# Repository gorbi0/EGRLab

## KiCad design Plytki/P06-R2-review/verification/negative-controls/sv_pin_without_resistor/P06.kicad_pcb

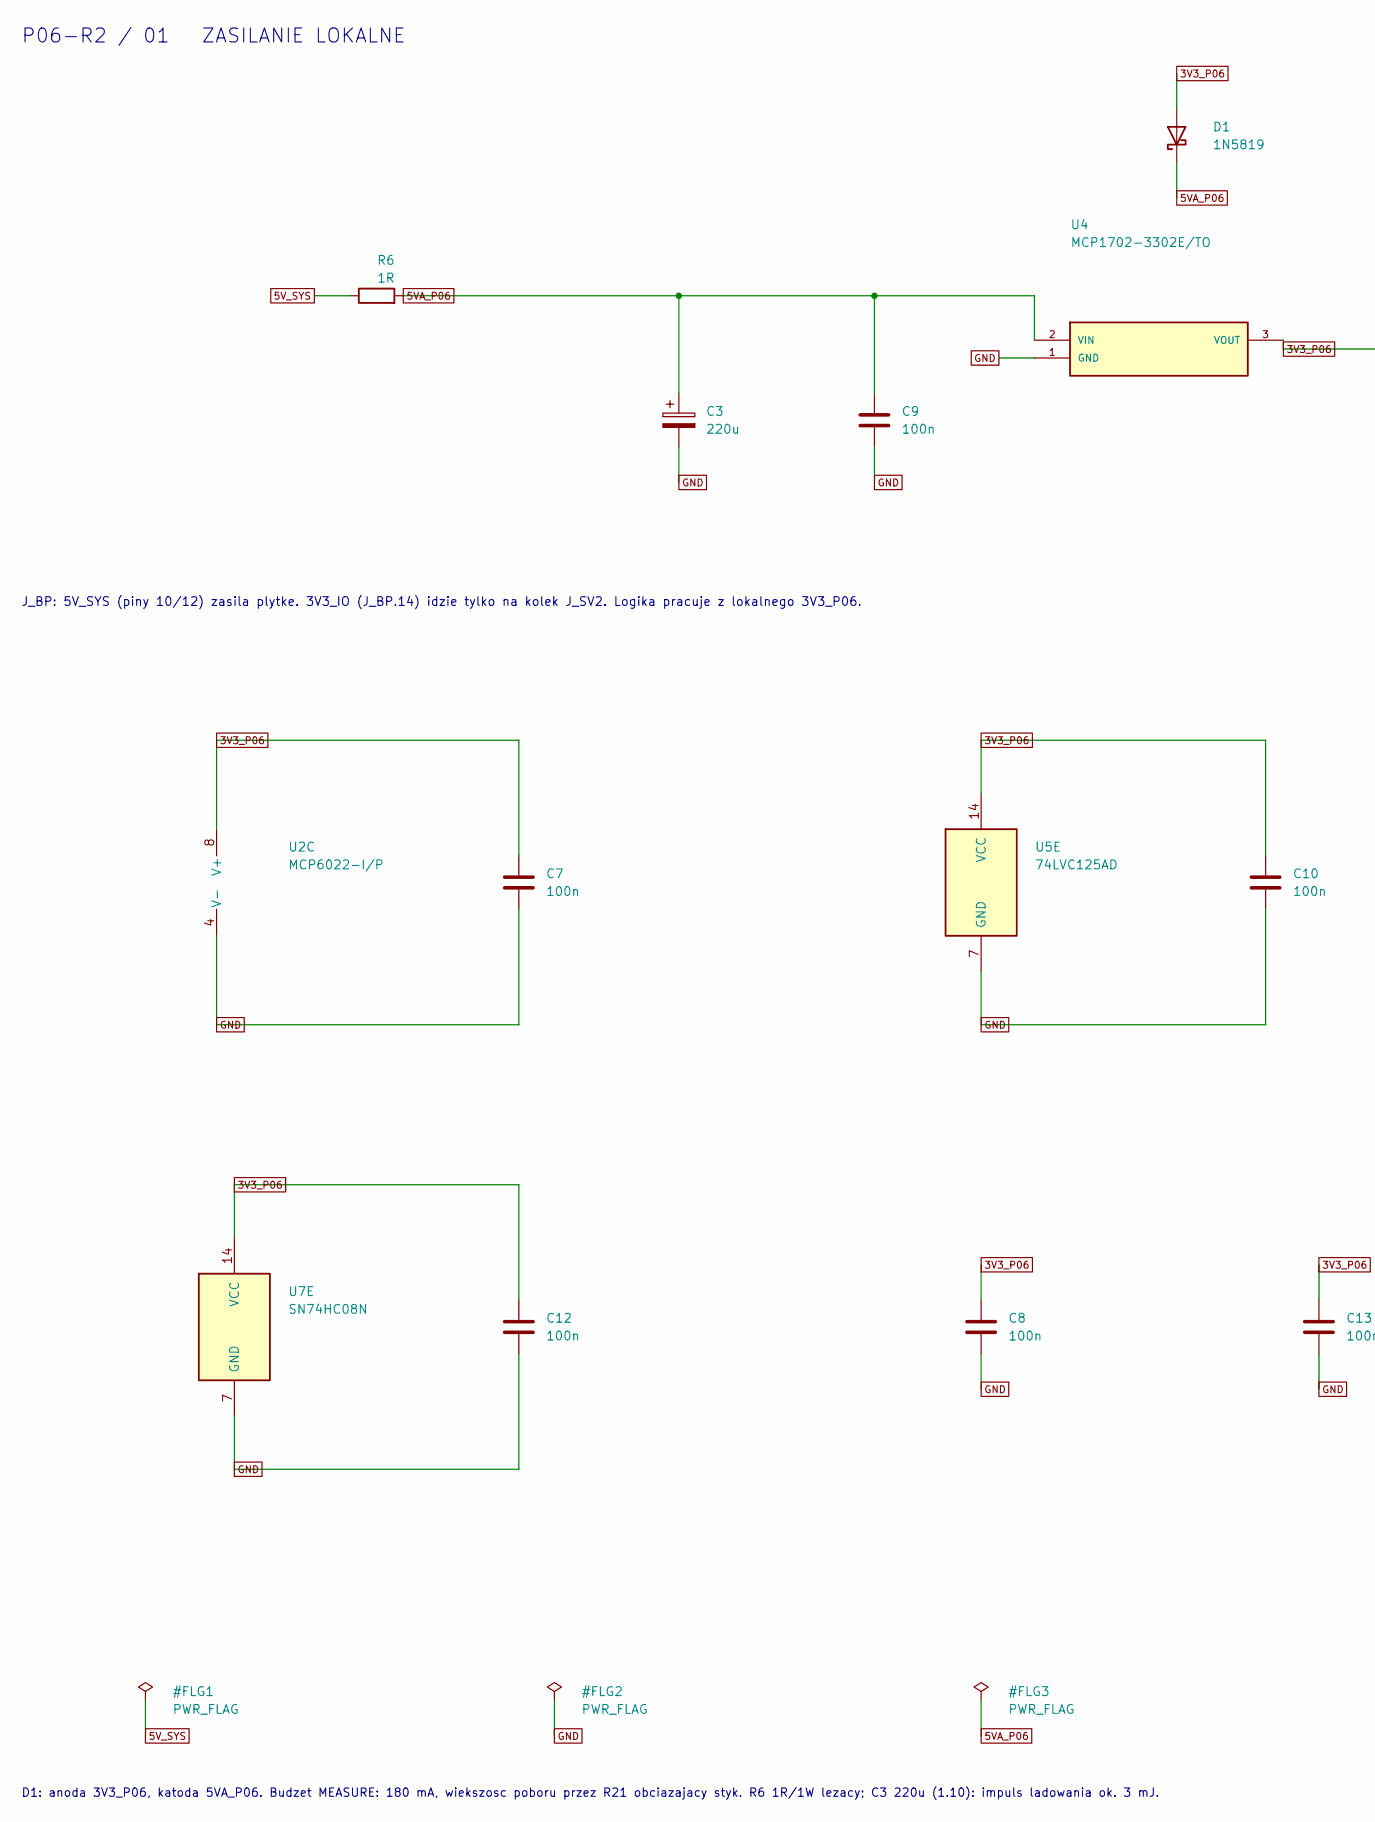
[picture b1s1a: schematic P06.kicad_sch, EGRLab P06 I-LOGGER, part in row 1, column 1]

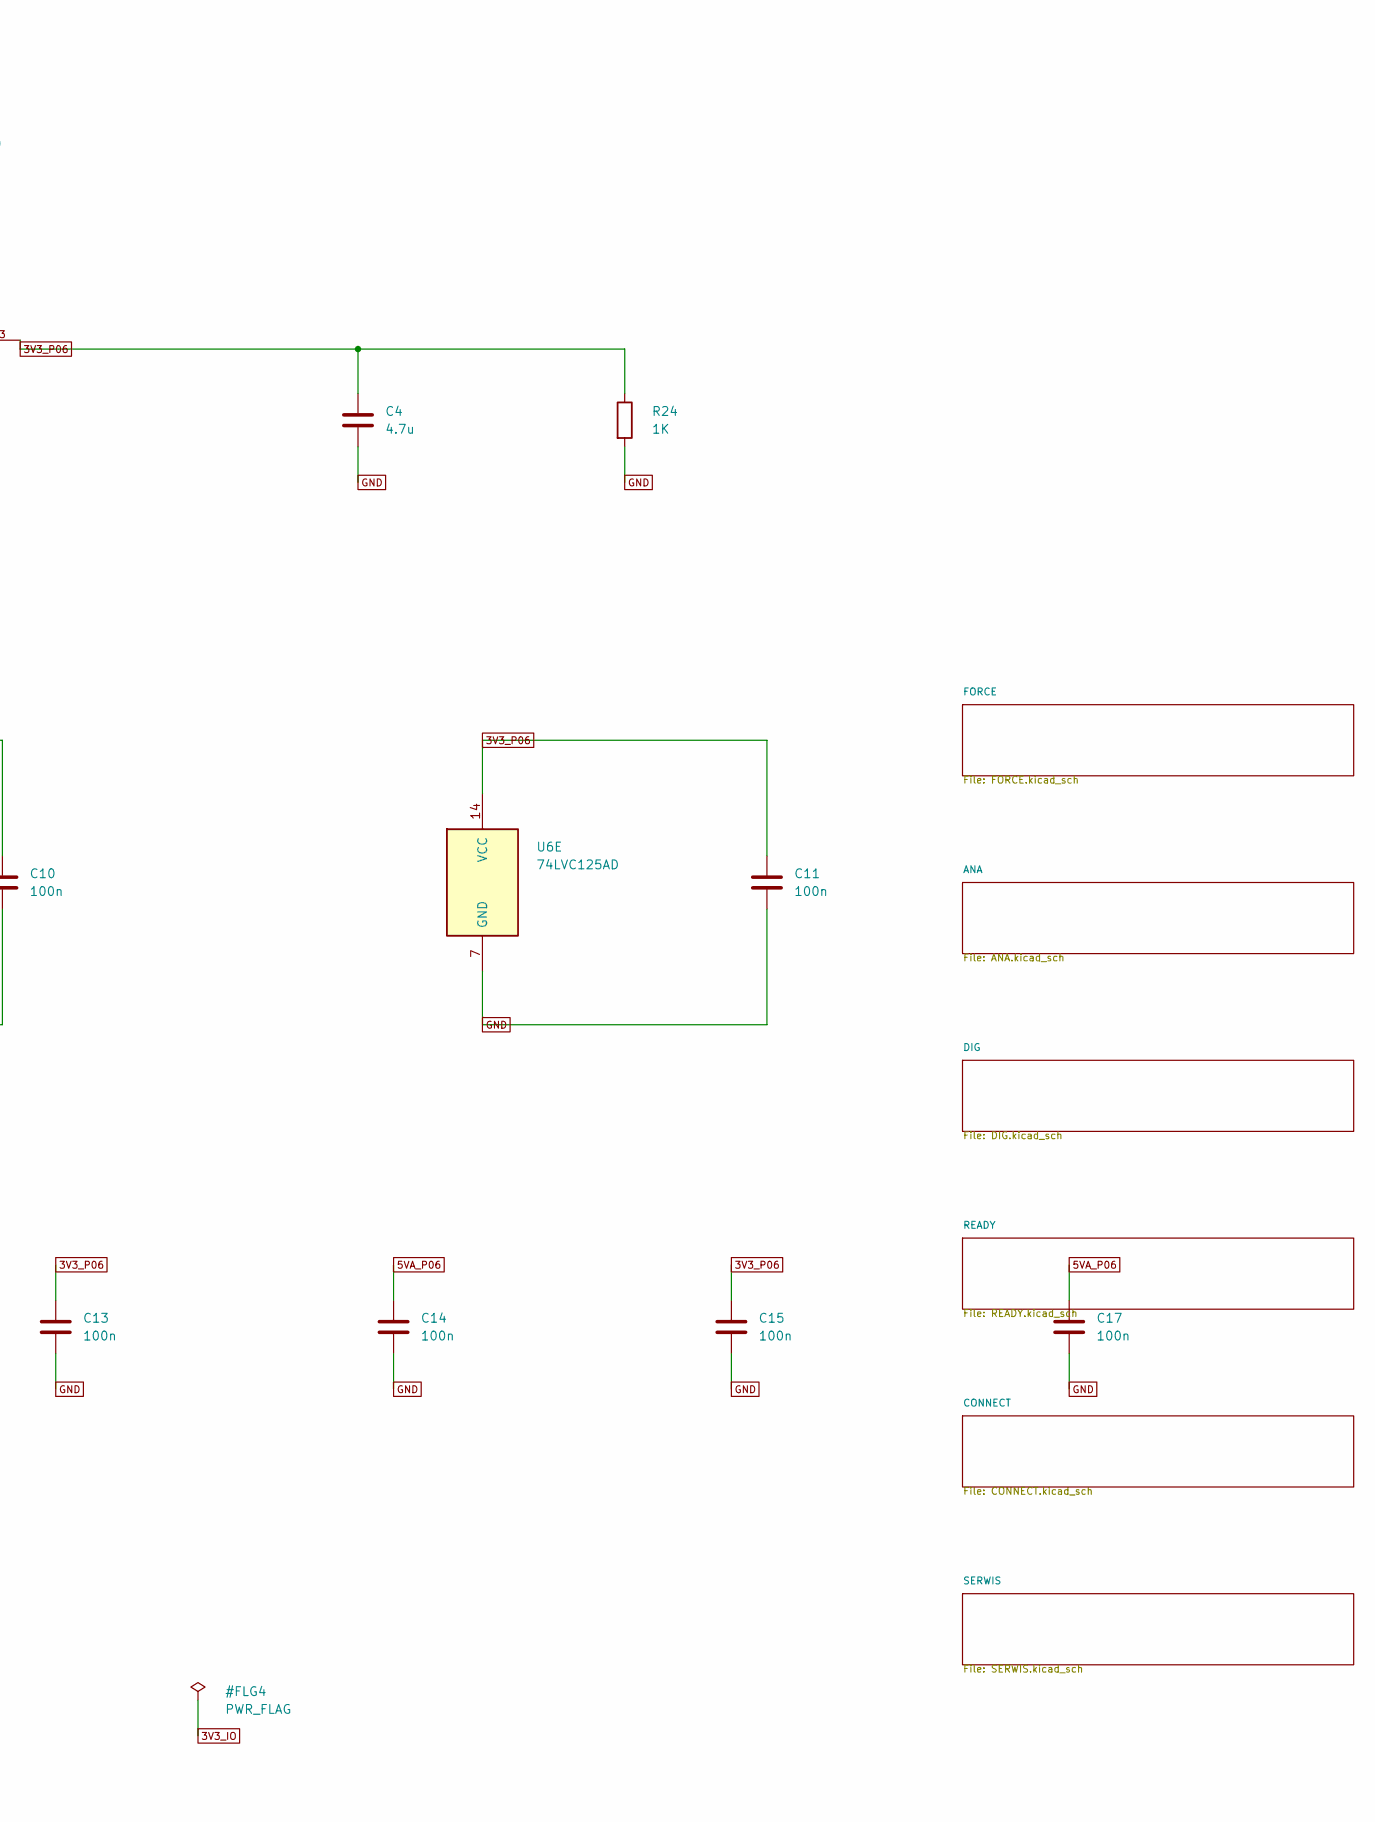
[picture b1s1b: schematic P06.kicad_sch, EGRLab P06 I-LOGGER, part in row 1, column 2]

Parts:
C3: 220u; CP_Radial_D6.3mm_P2.50mm; MPN EEUFR1C221
C4: 4.7u; C_1206_3216Metric_Pad1.33x1.80mm_HandSolder; MPN SMD 1206 X7R 25V 10% 4.7u
C7, C8, C9, C10, C11, C12, C13, C14, C15, C17: 100n; C_1206_3216Metric_Pad1.33x1.80mm_HandSolder; MPN SMD 1206 X7R 50V 10% 100n
D1: 1N5819; D_DO-41_SOD81_P10.16mm_Horizontal; MPN 1N5819
R6: 1R; R_Axial_DIN0411_L9.9mm_D3.6mm_P15.24mm_Horizontal; MPN KNP01U-1R (1R 1W wirewound, body 3x9mm)
R24: 1K; R_1206_3216Metric_Pad1.30x1.75mm_HandSolder; MPN RC1206FR-071KL
U2: MCP6022-I/P; DIP-8_W7.62mm; MPN MCP6022-I/P
U4: MCP1702-3302E/TO; TO-92_Inline_Wide; MPN MCP1702-3302E/TO
U5, U6: 74LVC125AD; SOIC-14_3.9x8.7mm_P1.27mm; MPN 74LVC125AD,118 (Nexperia)
U7: SN74HC08N; DIP-14_W7.62mm; MPN SN74HC08N

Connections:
3V3_P06: C4.1, C7.1, C8.1, C10.1, C11.1, C12.1, C13.1, C15.1, D1.2 (A), R24.1, U2.8 (V+), U4.3 (VOUT), U5.14 (VCC), U6.14 (VCC), U7.14 (VCC); also elsewhere on the board
5VA_P06: C3.1, C9.1, C14.1, C17.1, D1.1 (K), R6.2, U4.2 (VIN); also elsewhere on the board
/ANA/I_DIV: U2.3 (+); also elsewhere on the board
ADC_BUF: U2.1, U2.2 (-); also elsewhere on the board
GND: C3.2, C4.2, C7.2, C8.2, C9.2, C10.2, C11.2, C12.2, C13.2, C14.2, C15.2, C17.2, R24.2, U2.4 (V-), U4.1 (GND), U5.7 (GND), U6.7 (GND), U7.7 (GND); also elsewhere on the board
REF25: U2.5 (+); also elsewhere on the board
REF_BUF: U2.6 (-), U2.7; also elsewhere on the board

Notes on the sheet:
J_BP: 5V_SYS (piny 10/12) zasila plytke. 3V3_IO (J_BP.14) idzie tylko na kolek J_SV2. Logika pracuje z lokalnego 3V3_P06.
D1: anoda 3V3_P06, katoda 5VA_P06. Budzet MEASURE: 180 mA, wiekszosc poboru przez R21 obciazajacy styk. R6 1R/1W lezacy; C3 220u (1.10): impuls ladowania ok. 3 mJ.
P06-R2 / 01 ZASILANIE LOKALNE

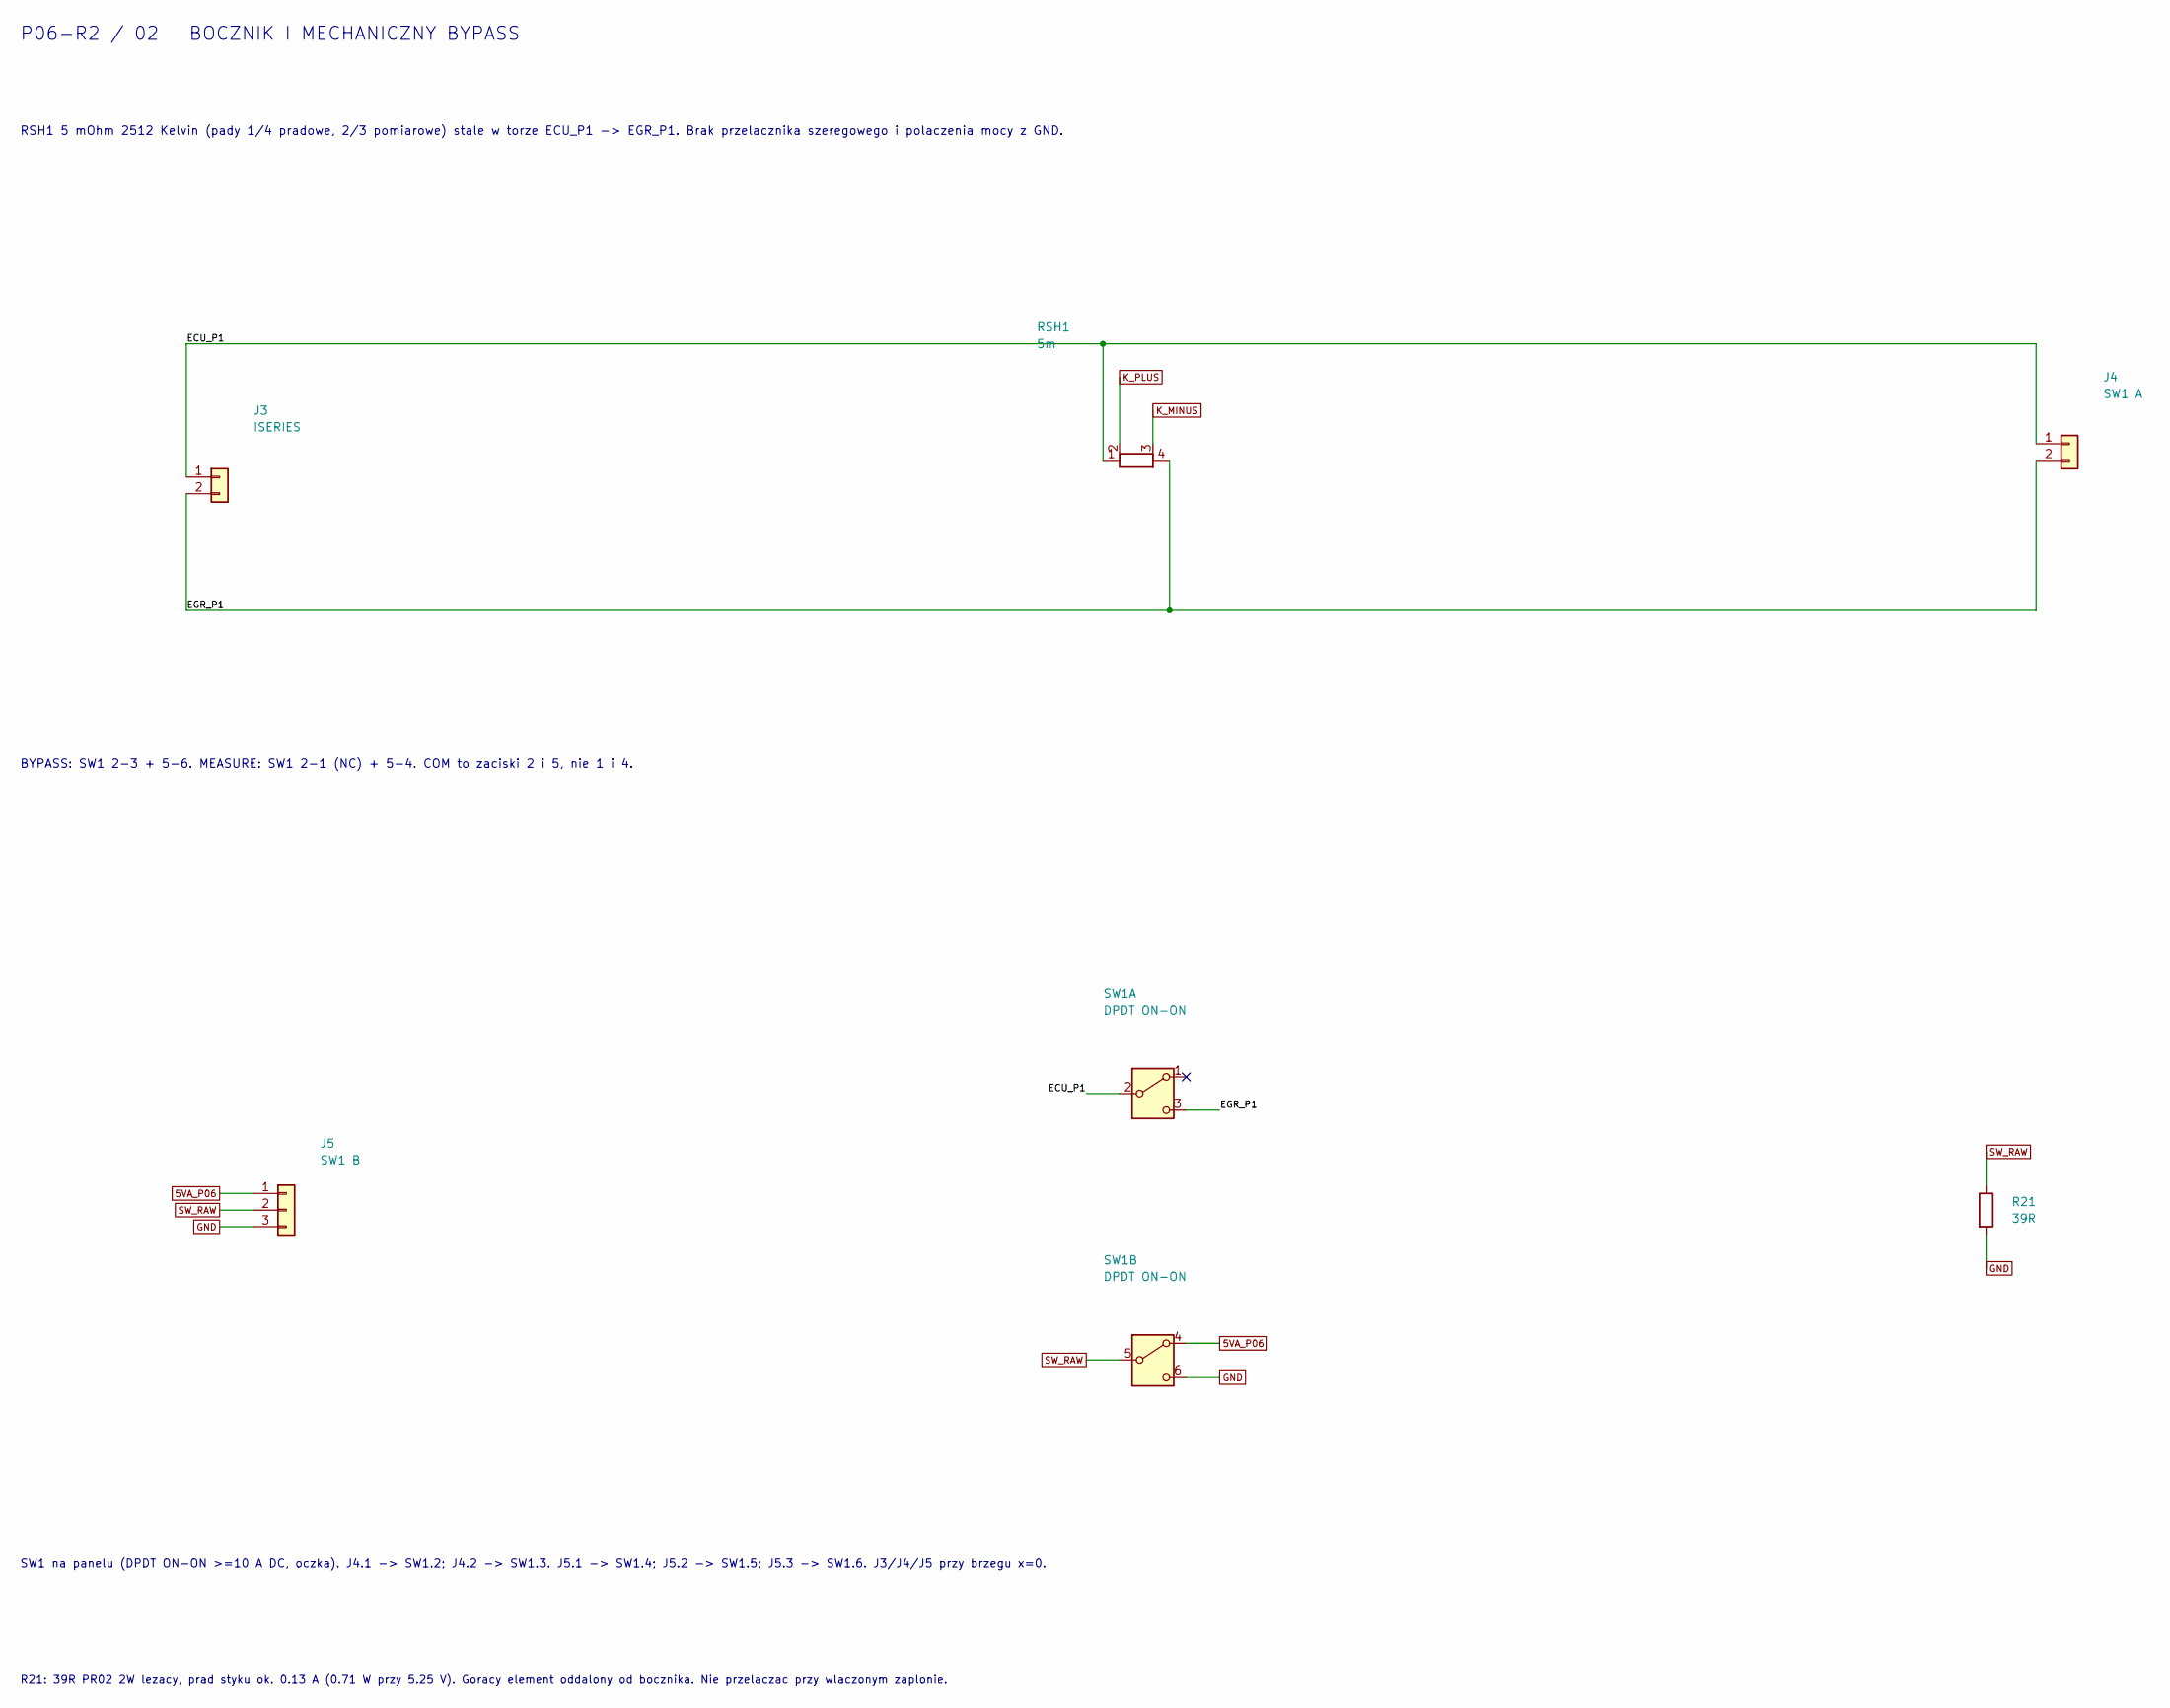
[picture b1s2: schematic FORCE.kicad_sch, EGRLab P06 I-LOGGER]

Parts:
J3: ISERIES; PTH_ISERIES; MPN Soldered harness
J4: SW1 A; PTH_BYPASS; MPN Soldered harness
J5: SW1 B; PTH_SWSTATUS; MPN Soldered harness
R21: 39R; R_PR02_P17.78; MPN PR02000203909JA100 (Vishay PR02 39R 5% 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
RSH1: 5m; R_Shunt_Vishay_WSK2512_T1.19mm_SenseE1.70; MPN WSK25125L000FEA (Vishay WSK2512, 5 mOhm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
SW1: DPDT ON-ON; OFFBOARD; MPN DPDT ON-ON panel toggle >=10A 12-30VDC,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

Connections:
5VA_P06: J5.1, SW1.4 (A); also elsewhere on the board
/FORCE/ECU_P1: J3.1, J4.1, RSH1.1, SW1.2 (B)
/FORCE/EGR_P1: J3.2, J4.2, RSH1.4, SW1.3 (C)
GND: J5.3, R21.2, SW1.6 (C); also elsewhere on the board
K_MINUS: RSH1.3; also elsewhere on the board
K_PLUS: RSH1.2; also elsewhere on the board
SW_RAW: J5.2, R21.1, SW1.5 (B); also elsewhere on the board

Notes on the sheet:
RSH1 5 mOhm 2512 Kelvin (pady 1/4 pradowe, 2/3 pomiarowe) stale w torze ECU_P1 -> EGR_P1. Brak przelacznika szeregowego i polaczenia mocy z GND.
BYPASS: SW1 2-3 + 5-6. MEASURE: SW1 2-1 (NC) + 5-4. COM to zaciski 2 i 5, nie 1 i 4.
SW1 na panelu (DPDT ON-ON >=10 A DC, oczka). J4.1 -> SW1.2; J4.2 -> SW1.3. J5.1 -> SW1.4; J5.2 -> SW1.5; J5.3 -> SW1.6. J3/J4/J5 przy brzegu x=0.
R21: 39R PR02 2W lezacy, prad styku ok. 0.13 A (0.71 W przy 5.25 V). Goracy element oddalony od bocznika. Nie przelaczac przy wlaczonym zaplonie.
P06-R2 / 02 BOCZNIK I MECHANICZNY BYPASS

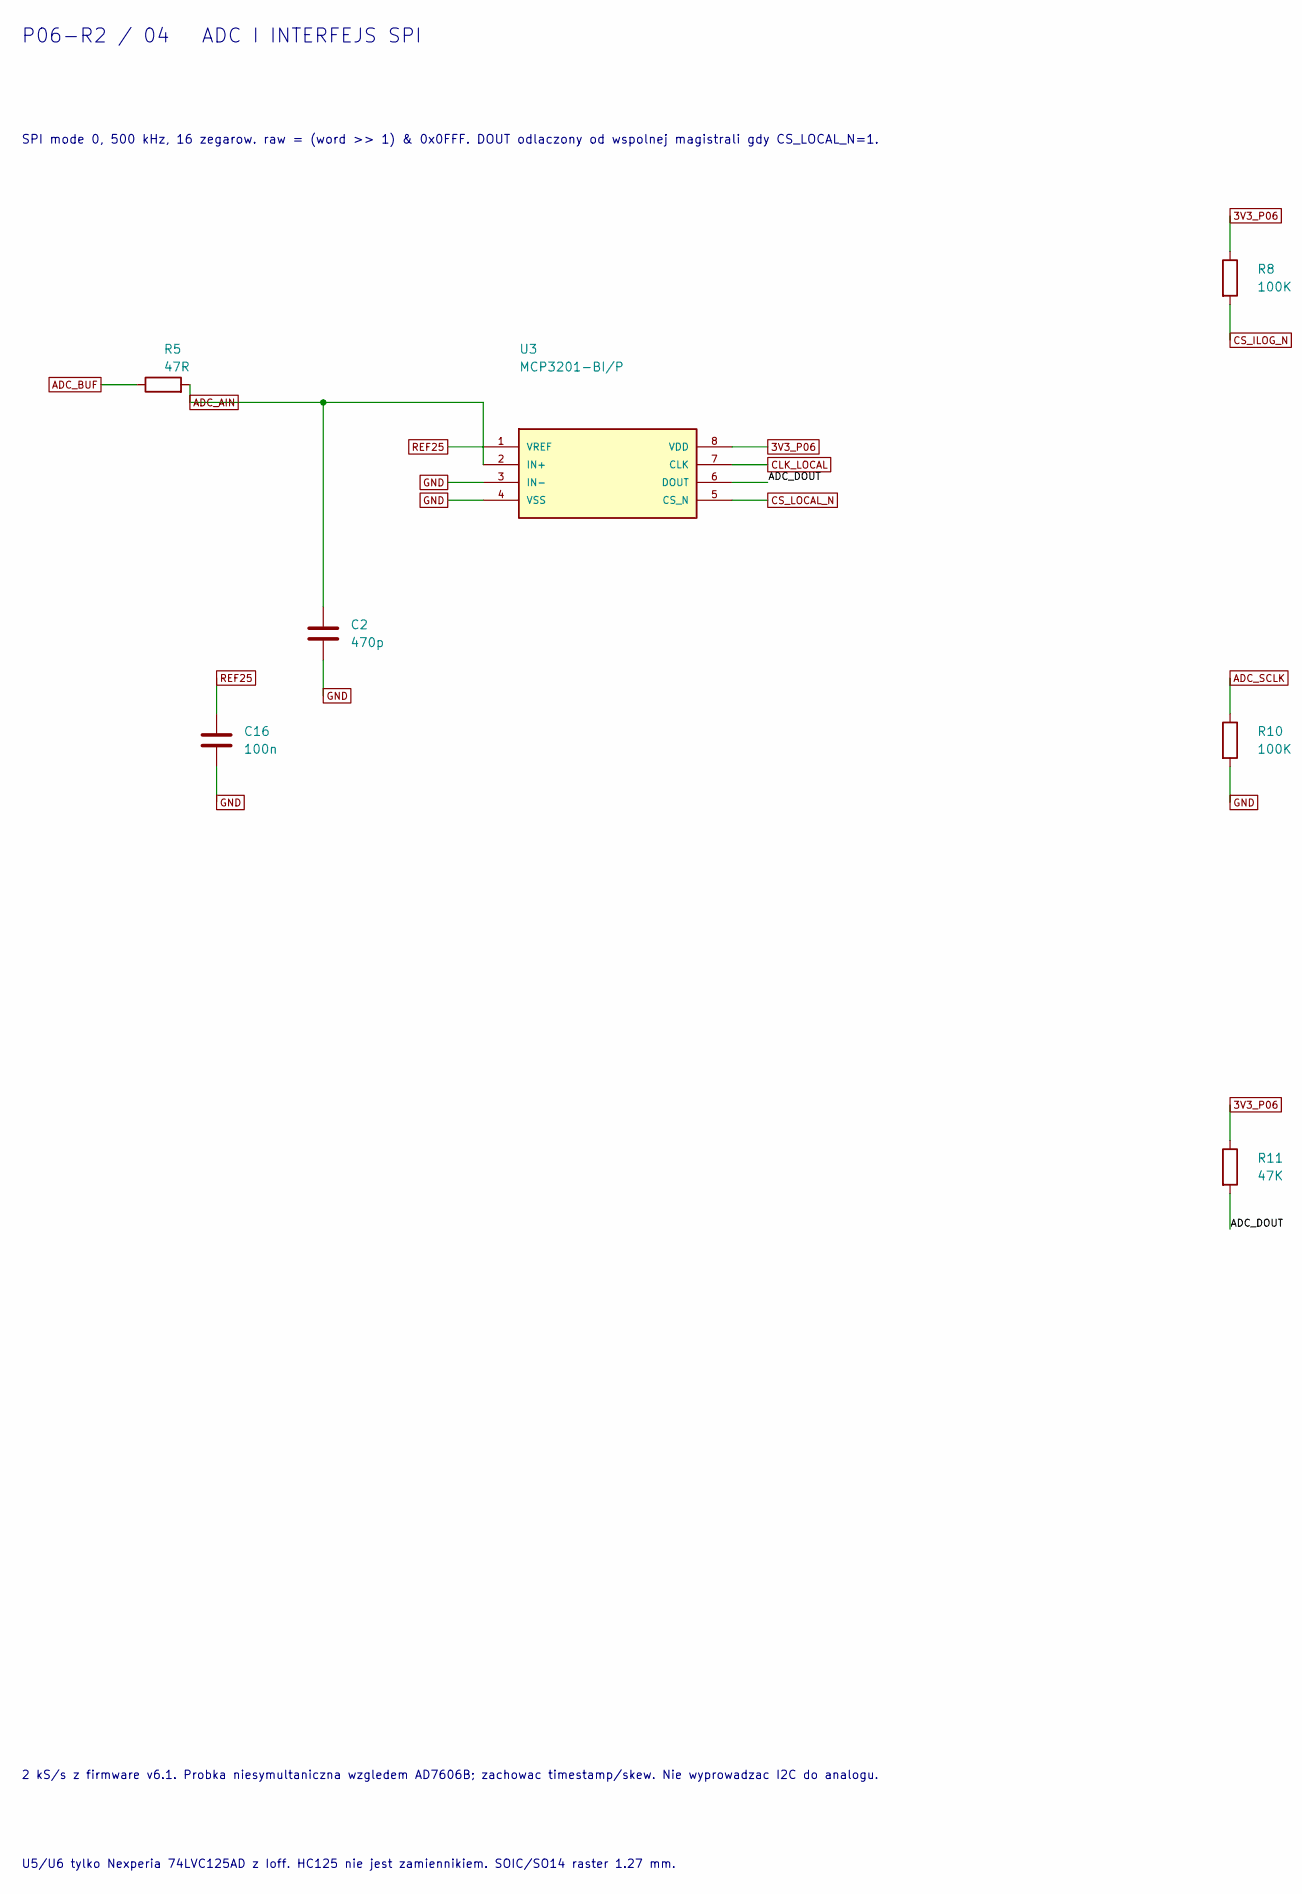
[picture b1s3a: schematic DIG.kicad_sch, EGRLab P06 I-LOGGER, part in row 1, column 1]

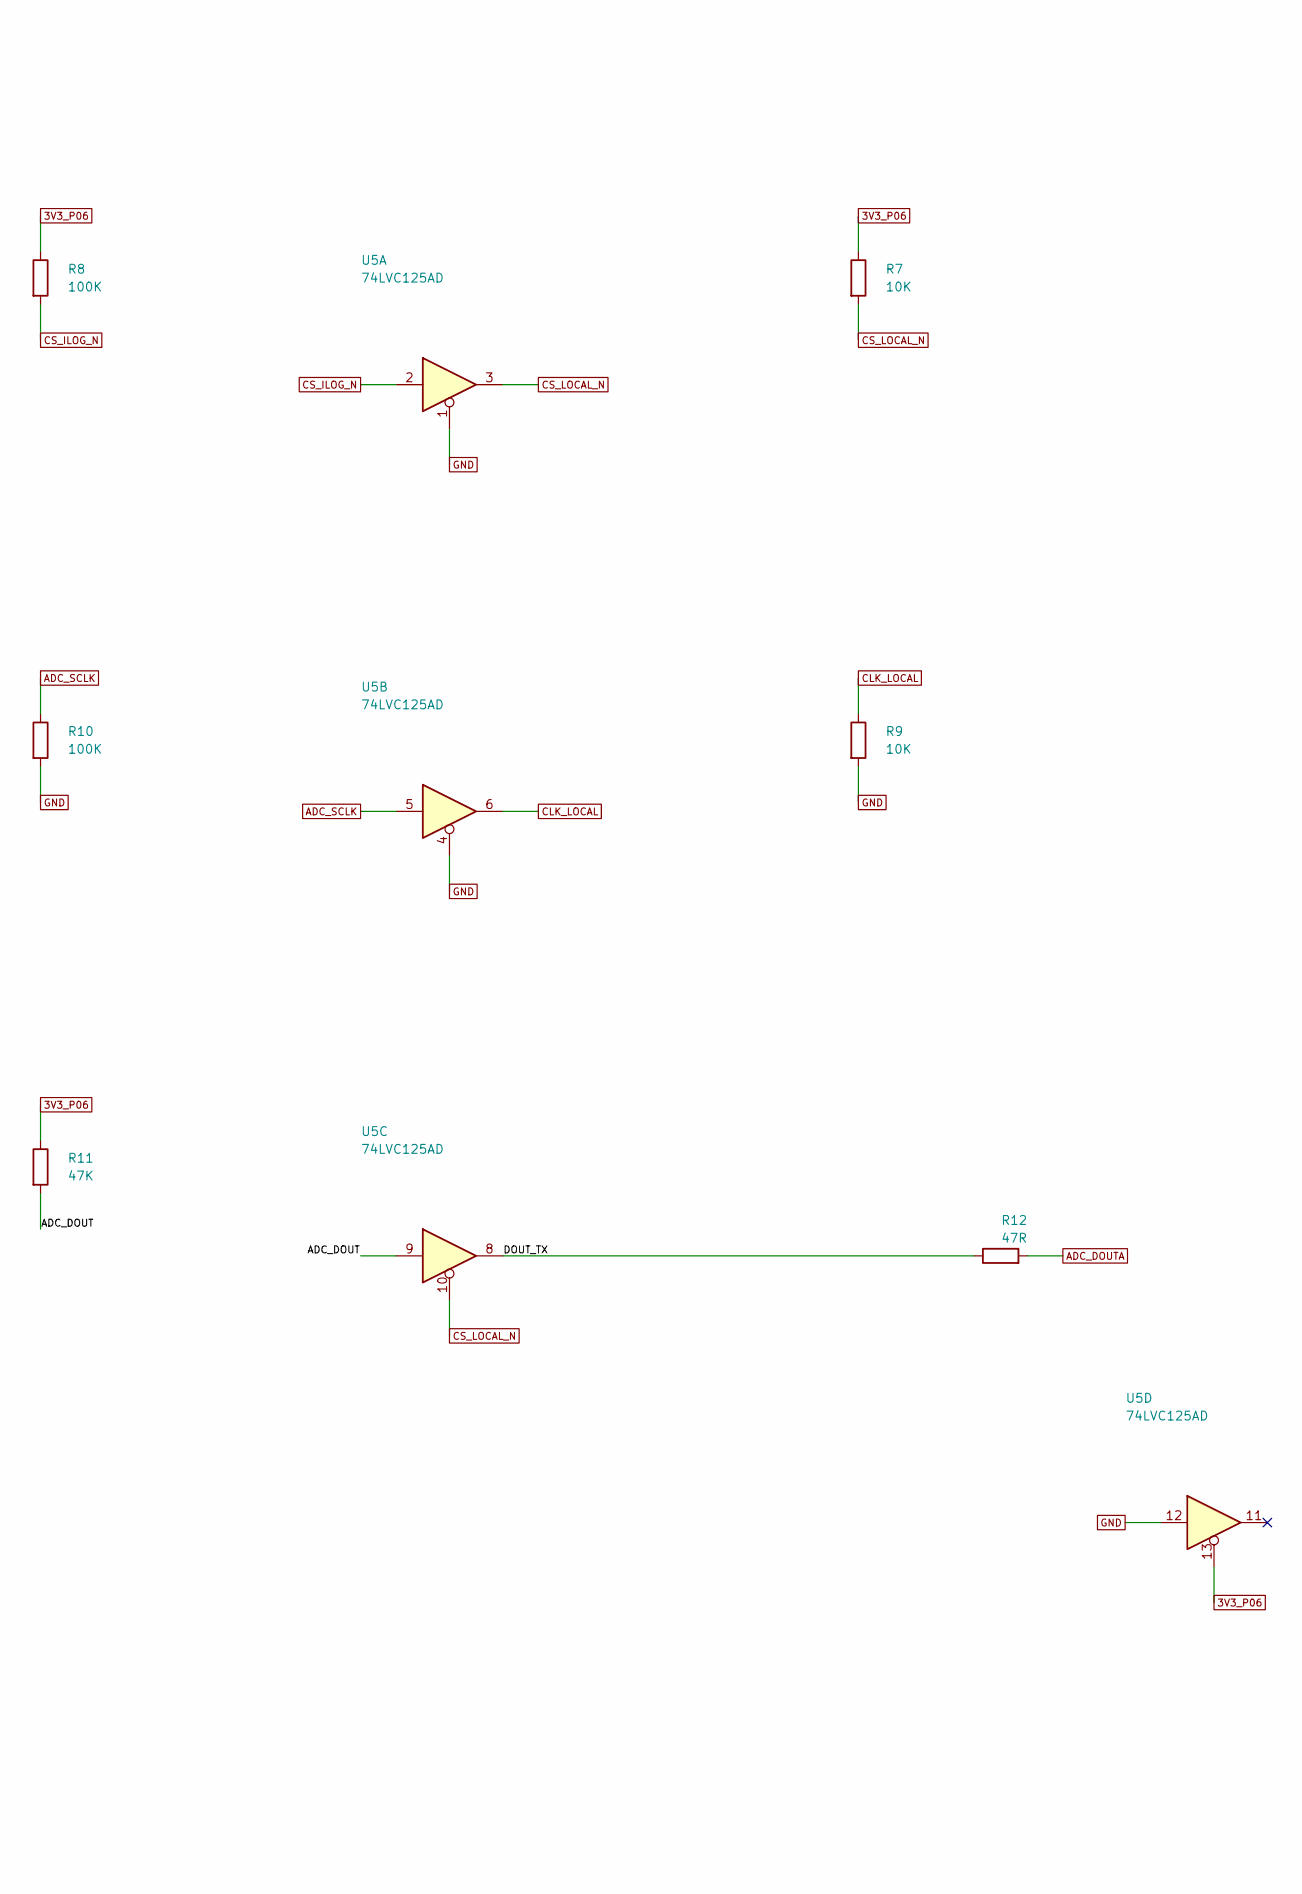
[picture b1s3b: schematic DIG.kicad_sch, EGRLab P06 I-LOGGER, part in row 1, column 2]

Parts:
C2: 470p; C_1206_3216Metric_Pad1.33x1.80mm_HandSolder; MPN SMD 1206 C0G 50V 5% 470p
C16: 100n; C_1206_3216Metric_Pad1.33x1.80mm_HandSolder; MPN SMD 1206 X7R 50V 10% 100n
R5, R12: 47R; R_1206_3216Metric_Pad1.30x1.75mm_HandSolder; MPN RC1206FR-0747RL
R7, R9: 10K; R_1206_3216Metric_Pad1.30x1.75mm_HandSolder; MPN RC1206FR-0710KL
R8, R10: 100K; R_1206_3216Metric_Pad1.30x1.75mm_HandSolder; MPN RC1206FR-07100KL
R11: 47K; R_Axial_DIN0207_L6.3mm_D2.5mm_P5.08mm_Vertical; MPN MF0207FTE-47K (Yageo MF0207 1% 0.6W, ow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
U3: MCP3201-BI/P; DIP-8_W7.62mm; MPN MCP3201-BI/P
U5: 74LVC125AD; SOIC-14_3.9x8.7mm_P1.27mm; MPN 74LVC125AD,118 (Nexperia)

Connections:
3V3_P06: R7.1, R8.1, R11.1, U3.8 (VDD), U5.13; also elsewhere on the board
/DIG/ADC_DOUT: R11.2, U3.6 (DOUT), U5.9
/DIG/DOUT_TX: R12.1, U5.8
ADC_AIN: C2.1, R5.2, U3.2 (IN+); also elsewhere on the board
ADC_BUF: R5.1; also elsewhere on the board
ADC_DOUTA: R12.2; also elsewhere on the board
ADC_SCLK: R10.1, U5.5; also elsewhere on the board
CLK_LOCAL: R9.1, U3.7 (CLK), U5.6; also elsewhere on the board
CS_ILOG_N: R8.2, U5.2; also elsewhere on the board
CS_LOCAL_N: R7.2, U3.5 (CS_N), U5.3, U5.10; also elsewhere on the board
GND: C2.2, C16.2, R9.2, R10.2, U3.3 (IN-), U3.4 (VSS), U5.1, U5.4, U5.12; also elsewhere on the board
REF25: C16.1, U3.1 (VREF); also elsewhere on the board

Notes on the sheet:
SPI mode 0, 500 kHz, 16 zegarow. raw = (word >> 1) & 0x0FFF. DOUT odlaczony od wspolnej magistrali gdy CS_LOCAL_N=1.
2 kS/s z firmware v6.1. Probka niesymultaniczna wzgledem AD7606B; zachowac timestamp/skew. Nie wyprowadzac I2C do analogu.
U5/U6 tylko Nexperia 74LVC125AD z Ioff. HC125 nie jest zamiennikiem. SOIC/SO14 raster 1.27 mm.
P06-R2 / 04 ADC I INTERFEJS SPI

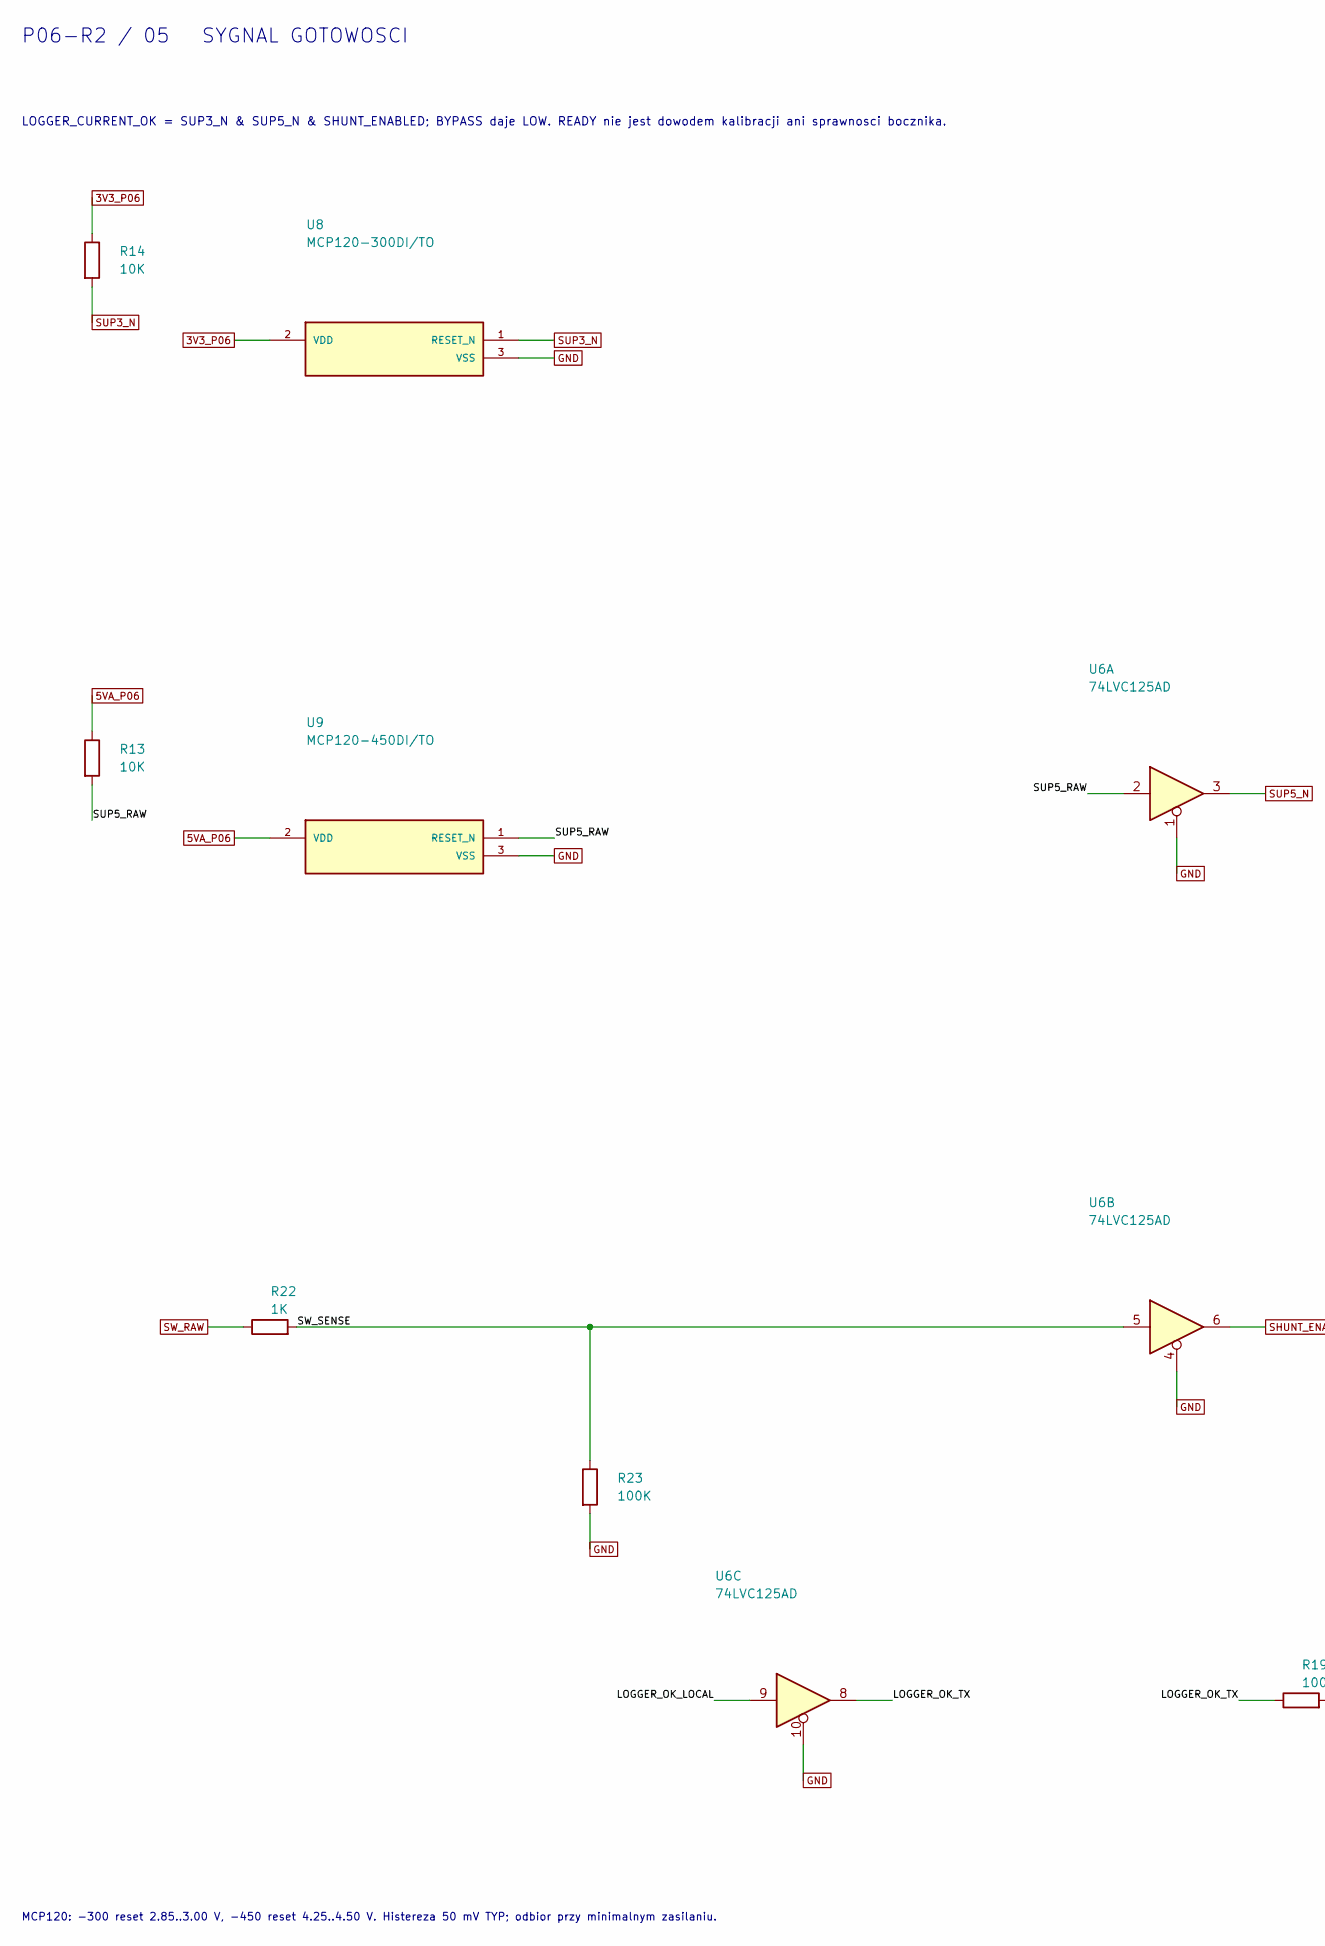
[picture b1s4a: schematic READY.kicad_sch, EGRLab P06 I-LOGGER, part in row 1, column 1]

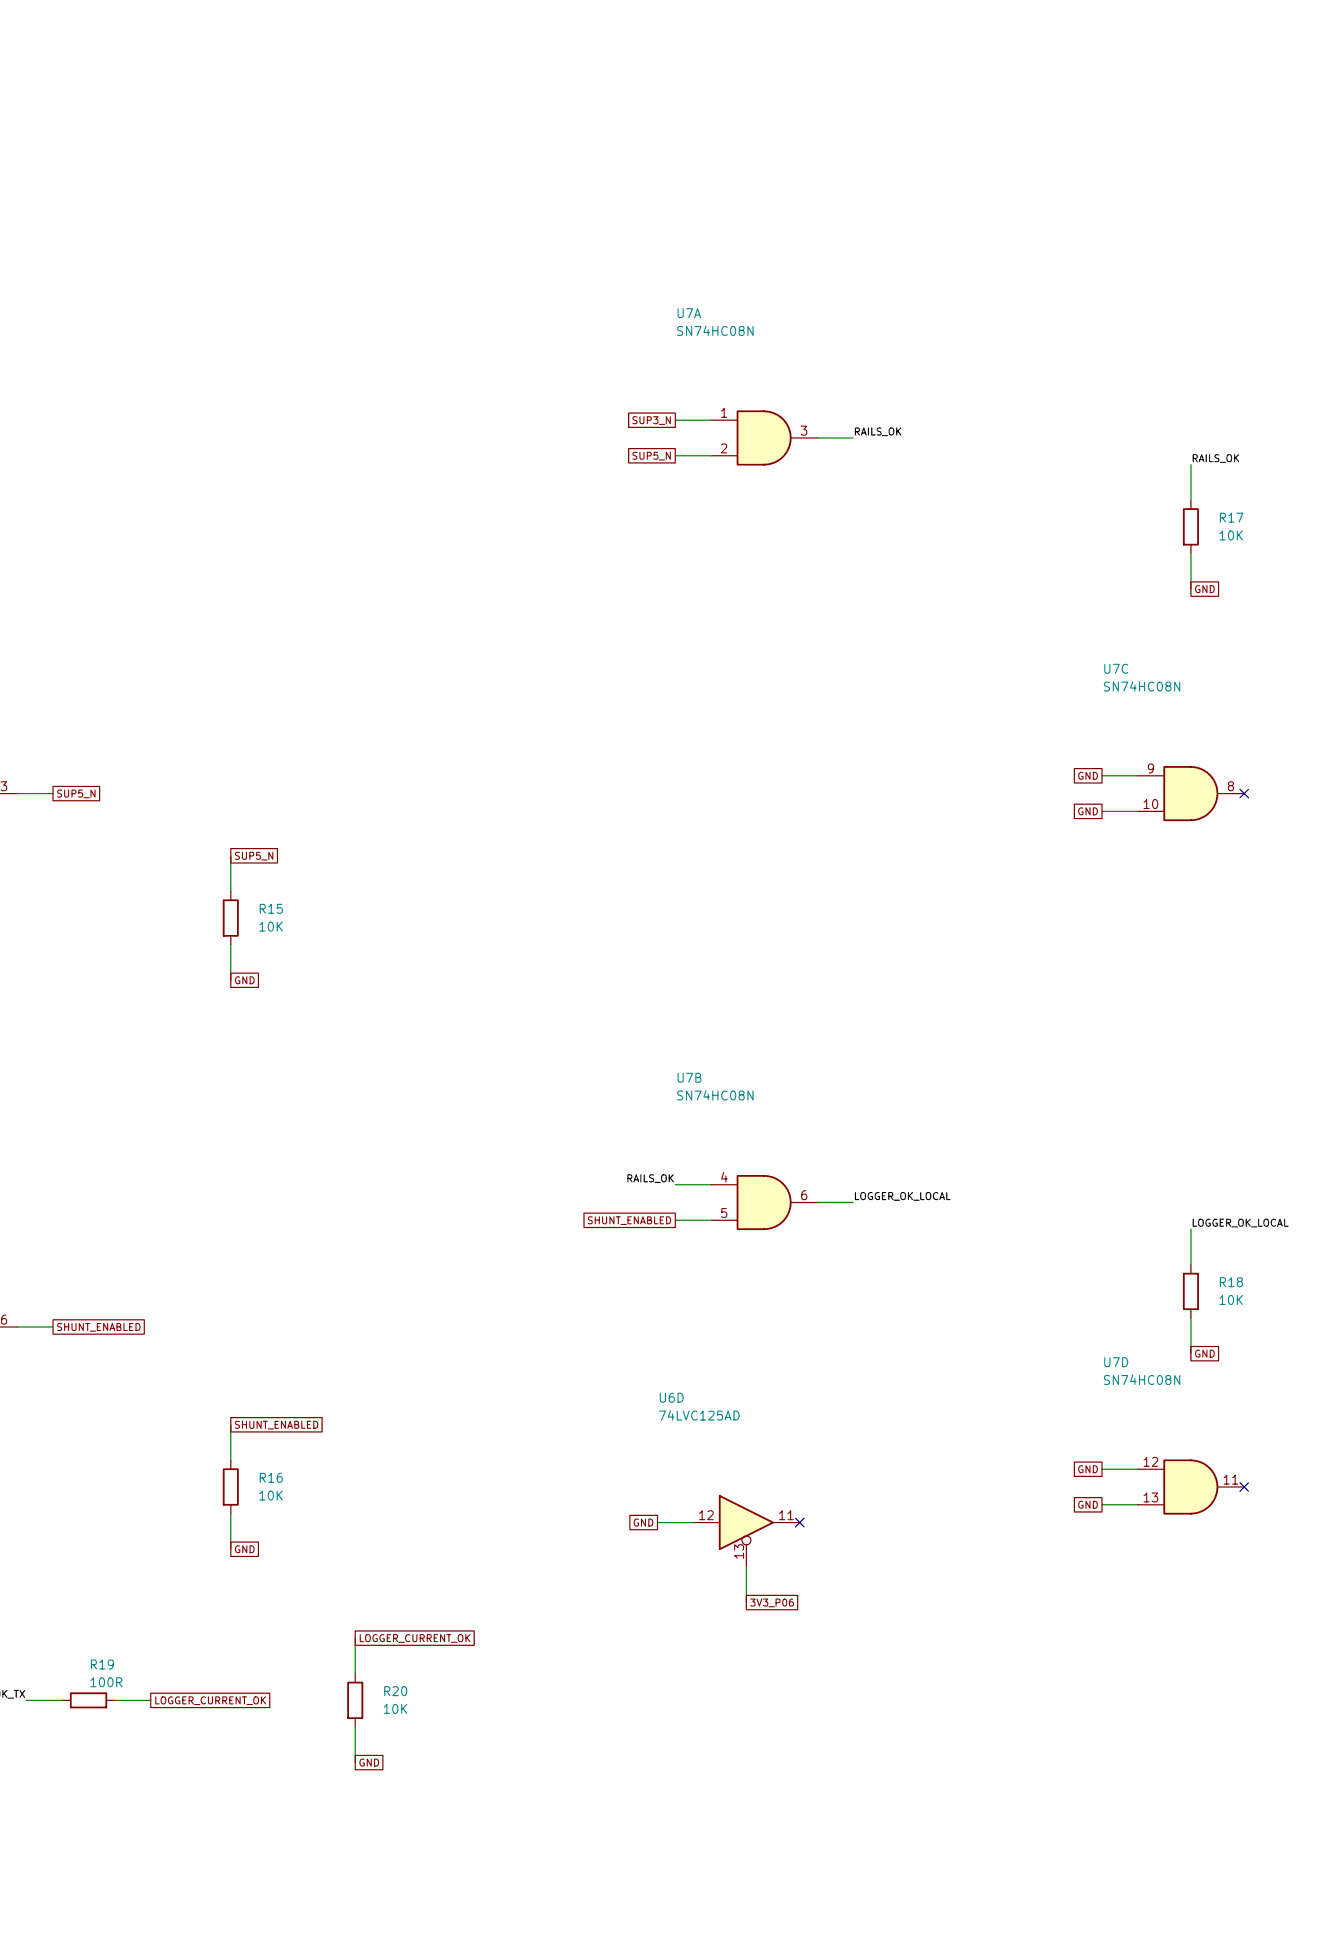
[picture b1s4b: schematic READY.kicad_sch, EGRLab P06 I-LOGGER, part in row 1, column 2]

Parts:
R13, R14, R15, R16, R17, R18, R20: 10K; R_1206_3216Metric_Pad1.30x1.75mm_HandSolder; MPN RC1206FR-0710KL
R19: 100R; R_1206_3216Metric_Pad1.30x1.75mm_HandSolder; MPN RC1206FR-07100RL
R22: 1K; R_1206_3216Metric_Pad1.30x1.75mm_HandSolder; MPN RC1206FR-071KL
R23: 100K; R_1206_3216Metric_Pad1.30x1.75mm_HandSolder; MPN RC1206FR-07100KL
U6: 74LVC125AD; SOIC-14_3.9x8.7mm_P1.27mm; MPN 74LVC125AD,118 (Nexperia)
U7: SN74HC08N; DIP-14_W7.62mm; MPN SN74HC08N
U8: MCP120-300DI/TO; TO-92_Inline_Wide; MPN MCP120-300DI/TO
U9: MCP120-450DI/TO; TO-92_Inline_Wide; MPN MCP120-450DI/TO

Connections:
3V3_P06: R14.1, U6.13, U8.2 (VDD); also elsewhere on the board
5VA_P06: R13.1, U9.2 (VDD); also elsewhere on the board
/READY/LOGGER_OK_LOCAL: R18.1, U6.9, U7.6
/READY/LOGGER_OK_TX: R19.1, U6.8
/READY/RAILS_OK: R17.1, U7.3, U7.4
/READY/SUP5_RAW: R13.2, U6.2, U9.1 (RESET_N)
/READY/SW_SENSE: R22.2, R23.1, U6.5
GND: R15.2, R16.2, R17.2, R18.2, R20.2, R23.2, U6.1, U6.4, U6.10, U6.12, U7.9, U7.10, U7.12, U7.13, U8.3 (VSS), U9.3 (VSS); also elsewhere on the board
LOGGER_CURRENT_OK: R19.2, R20.1; also elsewhere on the board
SHUNT_ENABLED: R16.1, U6.6, U7.5; also elsewhere on the board
SUP3_N: R14.2, U7.1, U8.1 (RESET_N); also elsewhere on the board
SUP5_N: R15.1, U6.3, U7.2; also elsewhere on the board
SW_RAW: R22.1; also elsewhere on the board

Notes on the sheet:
LOGGER_CURRENT_OK = SUP3_N & SUP5_N & SHUNT_ENABLED; BYPASS daje LOW. READY nie jest dowodem kalibracji ani sprawnosci bocznika.
MCP120: -300 reset 2.85..3.00 V, -450 reset 4.25..4.50 V. Histereza 50 mV TYP; odbior przy minimalnym zasilaniu.
P06-R2 / 05 SYGNAL GOTOWOSCI
